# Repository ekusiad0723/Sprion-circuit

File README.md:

# Sprion-circuit

## Outline
- This is my first gen micromouse circuit.
- It is made using [Kicad](https://www.kicad.xyz/).

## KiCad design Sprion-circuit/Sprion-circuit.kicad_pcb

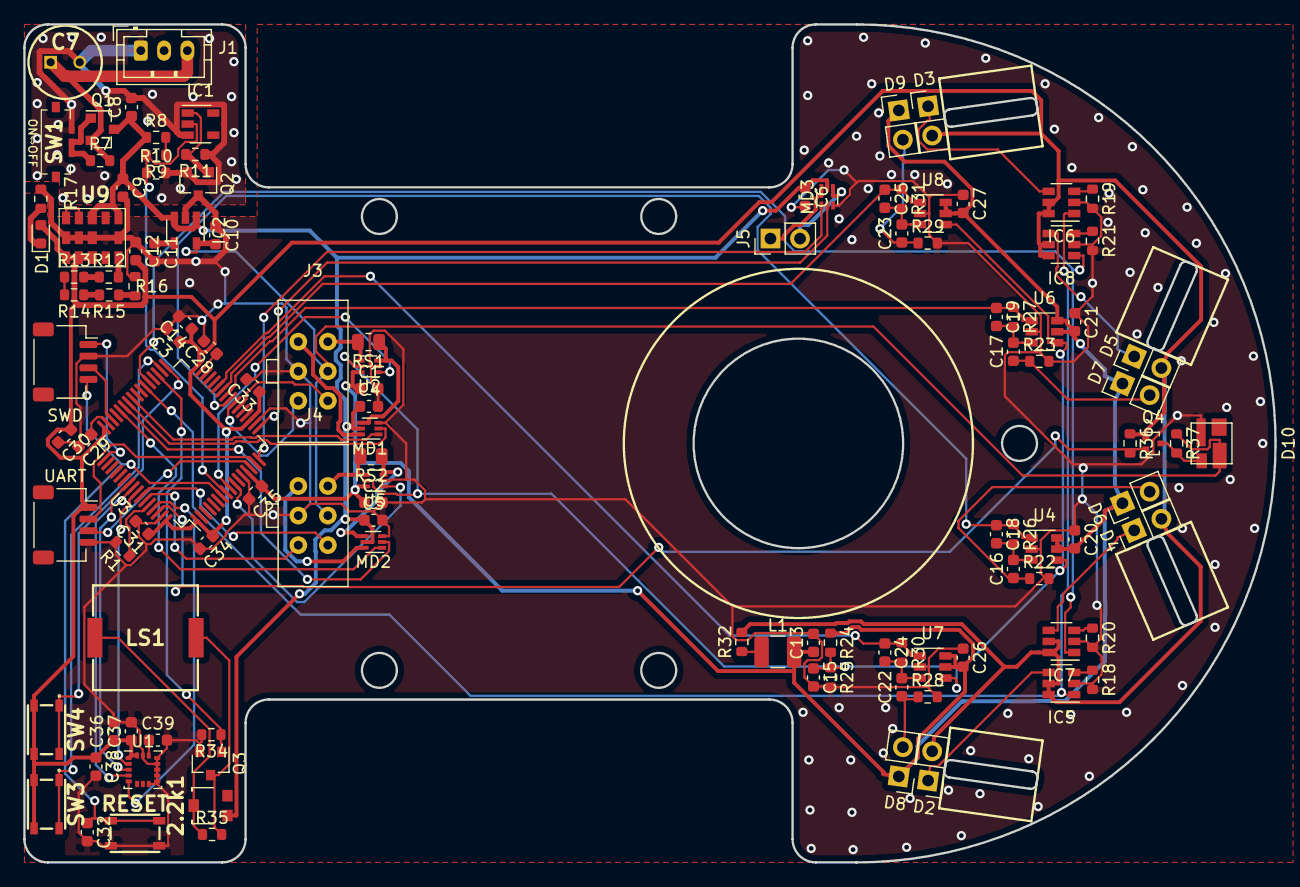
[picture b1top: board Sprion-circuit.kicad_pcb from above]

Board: 2 copper layers, 107.5 x 72.0 mm, 117 parts (0 on the bottom side), 83 nets.

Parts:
2.2k1: R_POT_TRIM; Potentiometer_SMD_PVZ3A
C1, C2, C3, C4, C5, C6, C8, C11, C15, C20, C21, C26, C27, C30, C31, C33, C34, C35, C36, C39: 0.1u; C_0603_1608Metric
C7: 100u; CAPPRD250W50D630H600
C9, C10, C12, C13: 10u; C_0603_1608Metric
C14: 4.7u; C_0603_1608Metric
C16, C17, C22, C23, C38: 0.01u; C_0603_1608Metric
C18, C19, C24, C25: 22p; C_0603_1608Metric
C28, C29, C37: 2.2u; C_0603_1608Metric
C32: C; C_0603_1608Metric
D1: LED; LED_0603_1608Metric
D2, D3, D4, D5: LED; PinHeader_1x02_P2.54mm_Vertical
D6, D7, D8, D9: D_Photo; PinHeader_1x02_P2.54mm_Vertical
D10: SK6812MINI
IC1: R3111N211A; SOT-23-5
IC2: TAR5SB50; SOT-23-5
IC5, IC6, IC7, IC8: NJU6080F1; SOT-23-6
J1: Conn_01x03_Female; JST_PH_B3B-PH-K_1x03_P2.00mm_Vertical
J3, J4: Conn_02x03_Odd_Even; 1717CXR+IE2-4096
J5: Conn_01x02_Female; PinHeader_1x02_P2.54mm_Vertical
L1: 47u; L_1210_3225Metric
LS1: Speaker; PKMCS
MD1, MD2, MD3: DRV8212_DRL; SOT-563
Q1: IRML6402; SOT-23
Q2, Q3: IRFML8244; SOT-23
Q4: RUE002N02; SOT-416
R1, R8, R9, R10, R24, R25, R34, R36, R37: 10k; R_0603_1608Metric
R7, R11, R22, R23, R28, R29: 100k; R_0603_1608Metric
R12, R35: 1k; R_0603_1608Metric
R13, R14, R15: 100; R_0603_1608Metric
R16: 10; R_0603_1608Metric
R17: 330; R_0603_1608Metric
R18, R19, R20, R21: R; R_0603_1608Metric
R26, R27, R30, R31: 220k; R_0603_1608Metric
R32: 2.7; R_0603_1608Metric
RESET: SW_Push; SMT_4.2X3.2_
RS1, RS2: 3m; R_0805_2012Metric
SW1: SSAJ120100; s
SW3, SW4: SW_Push; SMT_4.2X3.2_
SWD: Conn_01x04_Female; JST_SH_SM04B-SRSS-TB_1x04-1MP_P1.00mm_Horizontal
U1: ICM-20602; LGA-16_3x3mm_P0.5mm_LayoutBorder3x5y
U2, U5: INA185; SOT-563
U3: STM32F405RGTx; LQFP-64_10x10mm_P0.5mm
U4, U6, U7, U8: TLV9061; SOT-23-6
U9: LXDC55FAAA-203; LXDC55FAAA203
UART: Conn_01x04_Female; JST_SH_SM04B-SRSS-TB_1x04-1MP_P1.00mm_Horizontal

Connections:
+3.3VA: C1.1, C2.1, C13.1, C20.2, C21.2, C26.2, C27.2, C35.1, D6.1, D7.1, D8.1, D9.1, L1.2, R24.1, U2.6, U3.13, U4.5, U4.6, U5.6, U6.5, U6.6, U7.5, U7.6, U8.5, U8.6
+3V3: C3.1, C12.2, C14.1, C30.1, C31.1, C33.1, C34.1, C36.1, C37.1, C38.1, D1.2, D2.2, D3.2, D4.2, D5.2, IC5.5, IC5.6, IC6.5, IC6.6, IC7.5, IC7.6, IC8.5, IC8.6, Q4.1, R32.2, R36.1, SW3.2, SW4.2, U1.1, U1.16, U3.1, U3.19, U3.32, U3.48, U3.64, U9.7, U9.8, U9.9, UART.1
+5V: C10.2, D10.2, IC2.5, J3.4, J4.4, R37.1
+BATT: 2.2k1.1, C4.1, C5.1, C6.1, C8.1, C9.1, IC2.1, IC2.3, MD1.5, MD2.5, MD3.5, Q1.3, R8.1, U9.1, U9.3
/Controller/FULLCOLOR_LED: Q4.2, R36.2, U3.62
/Controller/IMU_MISO: U1.4, U3.56
/Controller/IMU_MOSI: U1.2, U3.57
/Controller/IMU_SCK: U1.3, U3.55
/Controller/IRLED_FRONT: IC7.1, IC8.1, U3.37
/Controller/IRLED_SIDE: IC5.1, IC6.1, U3.38
/Controller/MD1_CS: U2.1, U3.9
/Controller/MD1_IN1: MD1.1, U3.41
/Controller/MD1_IN2: MD1.2, U3.42
/Controller/MD2_CS: U3.10, U5.1
/Controller/MD2_IN1: MD2.2, U3.43
/Controller/MD_SUC_IN1: MD3.1, U3.16
/Controller/MD_SUC_IN2: MD3.2, U3.17
/Controller/RESET: C32.1, RESET.1, SWD.4, U3.7
/Controller/SENSOR_WALL_FL: C19.1, R27.1, U3.25, U6.1
/Controller/SENSOR_WALL_FR: C18.1, R26.1, U3.24, U4.1
/Controller/SENSOR_WALL_SL: C25.1, R31.1, U3.26, U8.1
/Controller/SENSOR_WALL_SR: C24.1, R30.1, U3.27, U7.1
/Controller/SPEAKER: Q3.1, R34.1, U3.35
/Controller/SW1: SW4.1, U3.33
/Controller/SW2: SW3.1, U3.34
/Controller/SWDCLK: SWD.1, U3.49
/Controller/SWDIO: SWD.3, U3.46
/Controller/UART_RX: U3.15, UART.2
/Controller/UART_TX: U3.14, UART.3
/DRV8212/ENC1_A: J3.6, U3.22
/DRV8212/ENC1_B: J3.5, U3.23
/DRV8212/ENC2_A: J4.6, U3.58
/DRV8212/ENC2_B: J4.5, U3.59
/DRV8212/MD2_IN1: MD2.1, U3.44
/IMU/CS: U1.5, U3.61
/Power/BAT: IC1.2, R9.2, R10.1, U3.8
GND: C1.2, C2.2, C3.2, C4.2, C5.2, C6.2, C9.2, C10.1, C11.2, C12.1, C13.2, C14.2, C15.2, C20.1, C21.1, C26.1, C27.1, C28.2, C29.2, C30.2, C31.2, C32.2, C33.2, C34.2, C35.2, C36.2, C37.2, C38.2, C39.2, D10.4, IC2.2, IC5.2, IC6.2, IC7.2, IC8.2, J3.3, J4.3, MD1.3, MD2.3, MD3.3, Q2.3, Q3.2, R1.2, R16.1, R17.2, R18.2, R19.2, R20.2, R21.2, R22.2, R23.2, R25.2, R28.2, R29.2, R34.2, RESET.2, SWD.2, U1.8, U1.9, U1.10, U1.11, U1.12, U1.13, U1.15, U2.2, U3.12, U3.18, U3.63, U4.2, U5.2, U6.2, U7.2, U8.2, U9.6, U9.12, U9.13, U9.14, UART.4
unnamed: 2.2k1.2, LS1.1, R35.1
unnamed: C7.1, J1.3, Q1.2, R7.2
unnamed: C7.2, C8.2, IC1.3, J1.1, Q2.2, R10.2, R11.1, SW1.1
unnamed: C11.1, IC2.4
unnamed: C16.1, D6.2, R22.1
unnamed: C16.2, C18.2, R26.2, U4.3
unnamed: C17.1, D7.2, R23.1
unnamed: C17.2, C19.2, R27.2, U6.3
unnamed: C22.1, D8.2, R28.1
unnamed: C22.2, C24.2, R30.2, U7.3
unnamed: C23.1, D9.2, R29.1
unnamed: C23.2, C25.2, R31.2, U8.3
unnamed: C28.1, U3.31
unnamed: C29.1, U3.47
unnamed: C39.1, U1.14
unnamed: D1.1, R17.1
unnamed: D2.1, IC5.4
unnamed: D3.1, IC6.4
unnamed: D4.1, IC7.4
unnamed: D5.1, IC8.4
unnamed: D10.1, Q4.3, R37.2
unnamed: IC1.1, Q2.1, R11.2
unnamed: IC5.3, R18.1
unnamed: IC6.3, R19.1
unnamed: IC7.3, R20.1
unnamed: IC8.3, R21.1
unnamed: J3.1, MD1.6
unnamed: J3.2, RS1.2, U2.4
unnamed: J4.1, MD2.6
unnamed: J4.2, RS2.2, U5.4
unnamed: J5.1, MD3.6
unnamed: J5.2, MD3.4
unnamed: L1.1, R32.1
unnamed: LS1.2, Q3.3, R35.2
unnamed: MD1.4, RS1.1, U2.3
unnamed: MD2.4, RS2.1, U5.3
unnamed: Q1.1, R7.1, SW1.2, SW1.3
unnamed: R1.1, U3.60
unnamed: R8.2, R9.1
unnamed: R12.1, R13.2
unnamed: R12.2, U9.11
unnamed: R13.1, R14.2
unnamed: R14.1, R15.2
unnamed: R15.1, R16.2
unnamed: U9.4, U9.5
VREF: C15.1, R24.2, R25.1, U2.5, U4.4, U5.5, U6.4, U7.4, U8.4

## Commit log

2021-06-22 とりま準備
2021-07-05 toriaezu
2021-07-05 今日のひはーさよおーなーらーまーたーあーうーひまでー
2021-07-06 電源でけたー！！
2021-07-06 ないしょくおわり
2021-07-07 デスクトップいくよーーー
2021-07-08 Push, Push, Push
2021-07-09 add wall sensor
2021-07-09 wall sensor
2021-11-14 :fix いろいろ
    後で書きます
    とりあえず寝ます
    許してください
2021-12-08 fix: MD周り,タイマー割り当て
    MDの書き方を変えた
    タイマー割り当てを再構成、対称性・高性能タイマーをどうするかみたいなとこ
2021-12-11 add,feat,fix:すまんコミットわすれててぐちゃぐちゃや
    配置始めた。
    フットプリント割り当てた
    回路図pdfで吐いた
2021-12-12 fix: eschemaの微修正
    ハイサイドスイッチをNch→Pchへ修正
    bootをプルダウンに
2021-12-13 fix add: 配置 回路の修正
    nju6080の出力の修正
    配置を完了
2021-12-14 feat: 配置の変更
2021-12-16 add fix feat: でけたー（コミットしてなくてごめん）
    ベタ塗、配線、再配置等
2021-12-16 fix: schematicを復元
    schematicのファイル
